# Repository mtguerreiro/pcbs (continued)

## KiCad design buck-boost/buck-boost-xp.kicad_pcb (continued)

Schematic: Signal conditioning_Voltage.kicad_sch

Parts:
C55, C73, C82: tbd; C_0805_2012Metric_Pad1.18x1.45mm_HandSolder
C72: dnp; C_0805_2012Metric_Pad1.18x1.45mm_HandSolder
C76: 1uF; C_0805_2012Metric_Pad1.18x1.45mm_HandSolder
C84: 10nF; C_0805_2012Metric_Pad1.18x1.45mm_HandSolder
R41, R63, R65, R66, R67, R68, R69, R70: tbd; R_0805_2012Metric_Pad1.20x1.40mm_HandSolder
U11: Opamp_Dual; SOIC-8_3.9x4.9mm_P1.27mm

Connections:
/I_out_+: R41.2; also elsewhere on the board
/Measurements/Voltage measurement/Sig_cond_volt_sens2/in_filt: R67.1, R68.1, U11.1, U11.2 (-)
/Measurements/Voltage measurement/Sig_cond_volt_sens2/out_: C72.1, R65.2, R67.2
/Measurements/Voltage measurement/Sig_cond_volt_sens2/out_filt: R66.2, R70.1
/V_dc_out_sens: R65.1, R66.1; also elsewhere on the board
GND: C55.1, C72.2, C76.2, C82.1, C84.2, R63.1, U11.4 (V-); also elsewhere on the board
unnamed: C73.1, R68.2, R69.1
unnamed: C55.2, R41.1, R63.2, U11.3 (+)
unnamed: C82.2, R69.2, U11.5 (+)
unnamed: C73.2, R70.2, U11.6 (-), U11.7
VDD: C76.1, C84.1, U11.8 (V+); also elsewhere on the board

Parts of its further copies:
C54, C56, C69, C78, C81, C83: tbd; C_0805_2012Metric_Pad1.18x1.45mm_HandSolder
C61, C88: 1uF; C_0805_2012Metric_Pad1.18x1.45mm_HandSolder
C62, C89: 10nF; C_0805_2012Metric_Pad1.18x1.45mm_HandSolder
C68, C77: dnp; C_0805_2012Metric_Pad1.18x1.45mm_HandSolder
R40, R42, R55, R56, R57, R58, R59, R60, R64, R72, R73, R74, R75, R76, R77, R78: tbd; R_0805_2012Metric_Pad1.20x1.40mm_HandSolder
U10, U12: Opamp_Dual; SOIC-8_3.9x4.9mm_P1.27mm

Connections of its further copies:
/I_in_-: R40.2; also elsewhere on the board
/Measurements/Voltage measurement/Sig_cond_volt_sens1/in_filt: R56.1, R57.1, U10.1, U10.2 (-)
/Measurements/Voltage measurement/Sig_cond_volt_sens1/out_: C68.1, R56.2, R60.2
/Measurements/Voltage measurement/Sig_cond_volt_sens1/out_filt: R59.1, R64.2
/Measurements/Voltage measurement/Sig_cond_volt_sens3/in_filt: R75.1, R76.1, U12.1, U12.2 (-)
/Measurements/Voltage measurement/Sig_cond_volt_sens3/out_: C77.1, R73.2, R75.2
/Measurements/Voltage measurement/Sig_cond_volt_sens3/out_filt: R74.2, R78.1
/V_dc_in_sens: R60.1, R64.1; also elsewhere on the board
/V_out: R42.2; also elsewhere on the board
/V_out_sens: R73.1, R74.1; also elsewhere on the board
GND: C54.1, C56.1, C61.2, C62.2, C68.2, C77.2, C81.1, C83.1, C88.2, C89.2, R55.1, R72.1, U10.4 (V-), U12.4 (V-); also elsewhere on the board
unnamed: C69.1, R57.2, R58.1
unnamed: C78.1, R76.2, R77.1
unnamed: C54.2, R40.1, R55.2, U10.3 (+)
unnamed: C81.2, R58.2, U10.5 (+)
unnamed: C69.2, R59.2, U10.6 (-), U10.7
unnamed: C56.2, R42.1, R72.2, U12.3 (+)
unnamed: C83.2, R77.2, U12.5 (+)
unnamed: C78.2, R78.2, U12.6 (-), U12.7
VDD: C61.1, C62.1, C88.1, C89.1, U10.8 (V+), U12.8 (V+); also elsewhere on the board

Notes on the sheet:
[3]
[5]
[1] This capacitor is for testing purposes. Ideally we would not need it, and we filter the signal afterwards anyways. [2] This RC network can be used to give some kind of low pass filter at the amplifier's output. Just remember that if you use this, the output is not buffered anymore. If the RC ne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
[1]
[2]
[4]

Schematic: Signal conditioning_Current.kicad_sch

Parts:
C85: dnp; C_0805_2012Metric_Pad1.18x1.45mm_HandSolder
C86, C87: tbd; C_0805_2012Metric_Pad1.18x1.45mm_HandSolder
C105: 1uF; C_0805_2012Metric_Pad1.18x1.45mm_HandSolder
C106: 10nF; C_0805_2012Metric_Pad1.18x1.45mm_HandSolder
R80, R81, R82, R83, R84, R85, R86: tbd; R_0805_2012Metric_Pad1.20x1.40mm_HandSolder
U15: Opamp_Dual; SOIC-8_3.9x4.9mm_P1.27mm

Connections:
/I_in_sens: R81.1, R82.1; also elsewhere on the board
/Measurements/Current measurement/I_in: R80.2, U15.3 (+); also elsewhere on the board
/Measurements/Current measurement/sig_cond_curr_sens1/in_filt: R83.1, R84.1, U15.1, U15.2 (-)
/Measurements/Current measurement/sig_cond_curr_sens1/out_: C85.1, R81.2, R83.2
/Measurements/Current measurement/sig_cond_curr_sens1/out_filt: R82.2, R86.1
GND: C85.2, C86.1, C105.2, C106.2, R80.1, U15.4 (V-); also elsewhere on the board
unnamed: C87.1, R84.2, R85.1
unnamed: C86.2, R85.2, U15.5 (+)
unnamed: C87.2, R86.2, U15.6 (-), U15.7
VDD: C105.1, C106.1, U15.8 (V+); also elsewhere on the board

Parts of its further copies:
C57, C58: dnp; C_0805_2012Metric_Pad1.18x1.45mm_HandSolder
C59, C60, C70, C71: tbd; C_0805_2012Metric_Pad1.18x1.45mm_HandSolder
C98, C100: 1uF; C_0805_2012Metric_Pad1.18x1.45mm_HandSolder
C99, C104: 10nF; C_0805_2012Metric_Pad1.18x1.45mm_HandSolder
R43, R44, R45, R46, R47, R48, R49, R50, R51, R61, R62, R71, R79, R87: tbd; R_0805_2012Metric_Pad1.20x1.40mm_HandSolder
U13, U14: Opamp_Dual; SOIC-8_3.9x4.9mm_P1.27mm

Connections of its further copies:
/IL_sens: R44.1, R61.1; also elsewhere on the board
/I_out_sens: R46.1, R47.1; also elsewhere on the board
/Measurements/Current measurement/I_L: R43.2, U13.3 (+); also elsewhere on the board
/Measurements/Current measurement/I_out: R45.2, U14.3 (+); also elsewhere on the board
/Measurements/Current measurement/sig_cond_curr_sens2/in_filt: R62.1, R71.1, U13.1, U13.2 (-)
/Measurements/Current measurement/sig_cond_curr_sens2/out_: C57.1, R44.2, R62.2
/Measurements/Current measurement/sig_cond_curr_sens2/out_filt: R61.2, R87.1
/Measurements/Current measurement/sig_cond_curr_sens3/in_filt: R48.1, R49.1, U14.1, U14.2 (-)
/Measurements/Current measurement/sig_cond_curr_sens3/out_: C58.1, R46.2, R48.2
/Measurements/Current measurement/sig_cond_curr_sens3/out_filt: R47.2, R51.1
GND: C57.2, C58.2, C59.1, C70.1, C98.2, C99.2, C100.2, C104.2, R43.1, R45.1, U13.4 (V-), U14.4 (V-); also elsewhere on the board
unnamed: C60.1, R49.2, R50.1
unnamed: C71.1, R71.2, R79.1
unnamed: C70.2, R79.2, U13.5 (+)
unnamed: C71.2, R87.2, U13.6 (-), U13.7
unnamed: C59.2, R50.2, U14.5 (+)
unnamed: C60.2, R51.2, U14.6 (-), U14.7
VDD: C98.1, C99.1, C100.1, C104.1, U13.8 (V+), U14.8 (V+); also elsewhere on the board

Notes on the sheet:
[5]
[1] This pull-down resistor was placed here just to present some kind of small load to the sensor's output. Also, this prevents the amplifier's input to ever float. I'm not really sure whether this makes a difference or not. [Future notes: maybe it is better to move this resistor to the output of t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
[3]
[1]
[2]
[4]

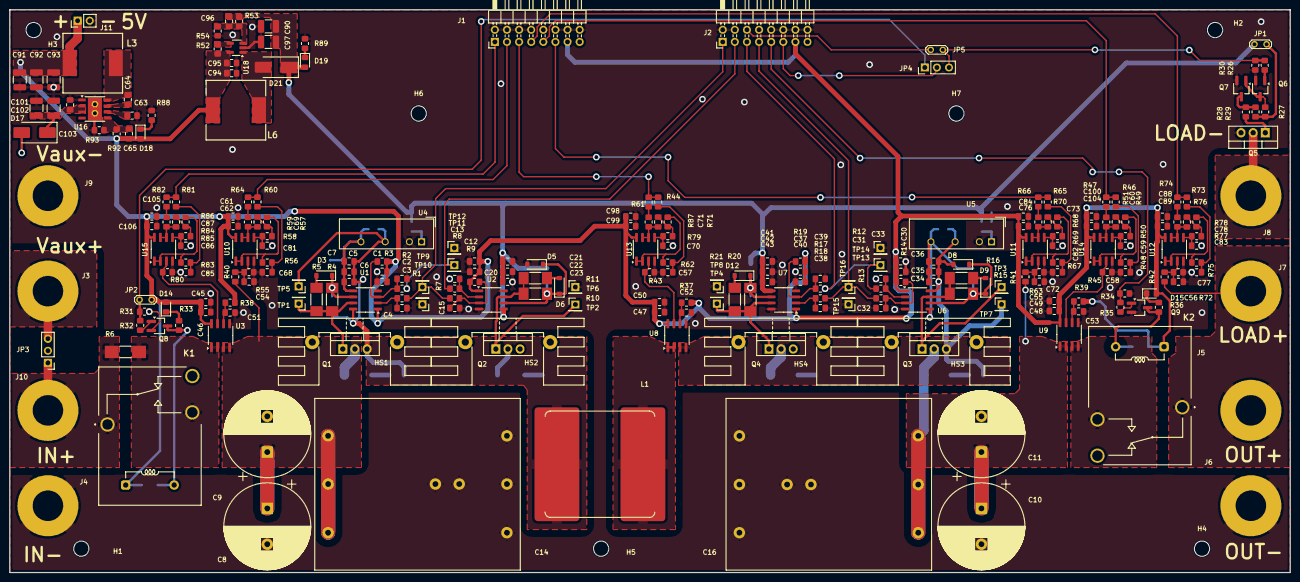
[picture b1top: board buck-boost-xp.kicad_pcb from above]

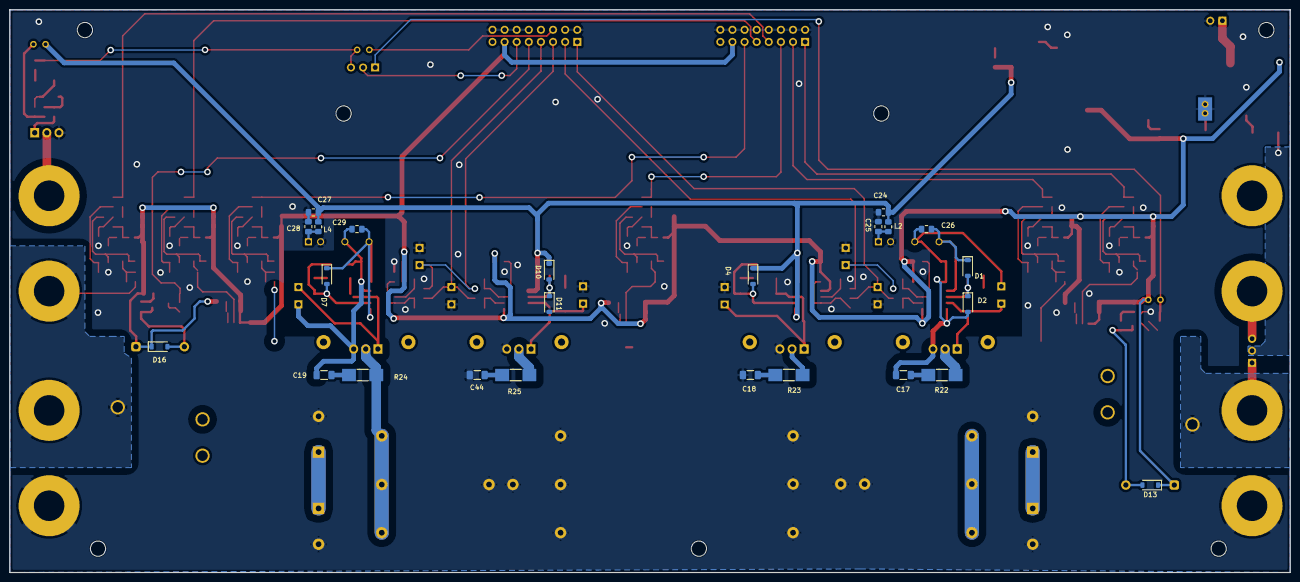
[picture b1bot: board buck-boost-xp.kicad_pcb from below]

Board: 2 copper layers, 268.5 x 118.0 mm, 287 parts (24 on the bottom side), 124 nets.

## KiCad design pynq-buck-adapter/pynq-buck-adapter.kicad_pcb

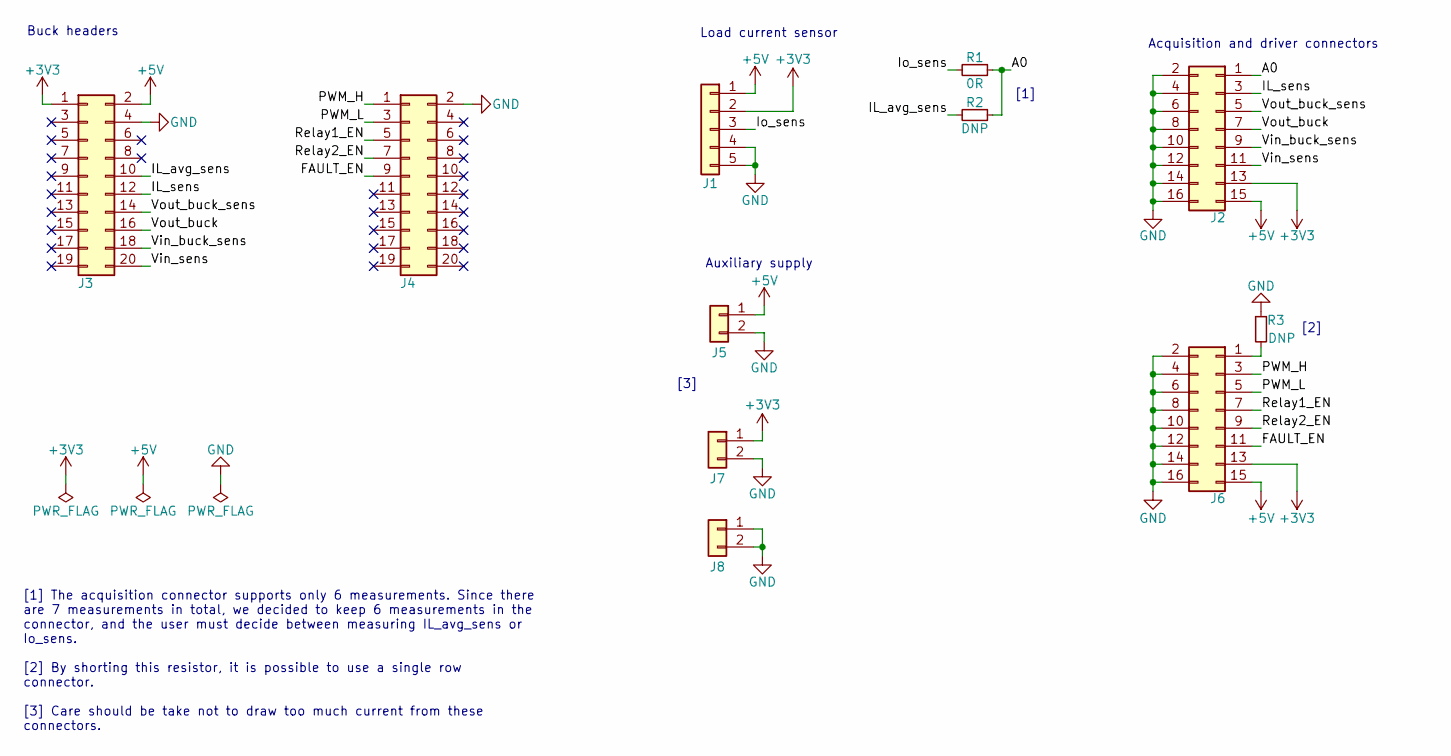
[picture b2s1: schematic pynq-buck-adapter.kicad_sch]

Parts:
J1: Conn_01x05; PinHeader_1x05_P2.54mm_Vertical
J2, J6: Conn_02x08_Odd_Even; PinHeader_2x08_P2.54mm_Horizontal
J3, J4: Conn_02x10_Odd_Even; PinHeader_2x10_P2.54mm_Vertical
J5, J7, J8: Conn_01x02; PinHeader_1x02_P2.54mm_Vertical
R1: 0R; R_0805_2012Metric_Pad1.20x1.40mm_HandSolder
R2, R3: DNP; R_0805_2012Metric_Pad1.20x1.40mm_HandSolder

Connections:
+3V3: J1.2, J2.13, J3.1, J6.13, J7.1
+5V: J1.1, J2.15, J3.2, J5.1, J6.15
/A0: J2.1, R1.1, R2.1
/FAULT_EN: J4.9, J6.11
/IL_avg_sens: J3.10, R2.2
/IL_sens: J2.3, J3.12
/Io_sens: J1.3, R1.2
/PWM_H: J4.1, J6.3
/PWM_L: J4.3, J6.5
/Relay1_EN: J4.5, J6.7
/Relay2_EN: J4.7, J6.9
/Vin_buck_sens: J2.9, J3.18
/Vin_sens: J2.11, J3.20
/Vout_buck: J2.7, J3.16
/Vout_buck_sens: J2.5, J3.14
GND: J1.4, J1.5, J2.2, J2.4, J2.6, J2.8, J2.10, J2.12, J2.14, J2.16, J3.4, J4.2, J5.2, J6.2, J6.4, J6.6, J6.8, J6.10, J6.12, J6.14, J6.16, J7.2, J8.1, J8.2, R3.1
unnamed: J6.1, R3.2

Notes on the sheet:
[1] The acquisition connector supports only 6 measurements. Since there are 7 measurements in total, we decided to keep 6 measurements in the connector, and the user must decide between measuring IL_avg_sens or Io_sens. [2] By shorting this resistor, it is possible to use a single row connector. [3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
[2]
[1]
Load current sensor
[3]
Buck headers
Acquisition and driver connectors
Auxiliary supply

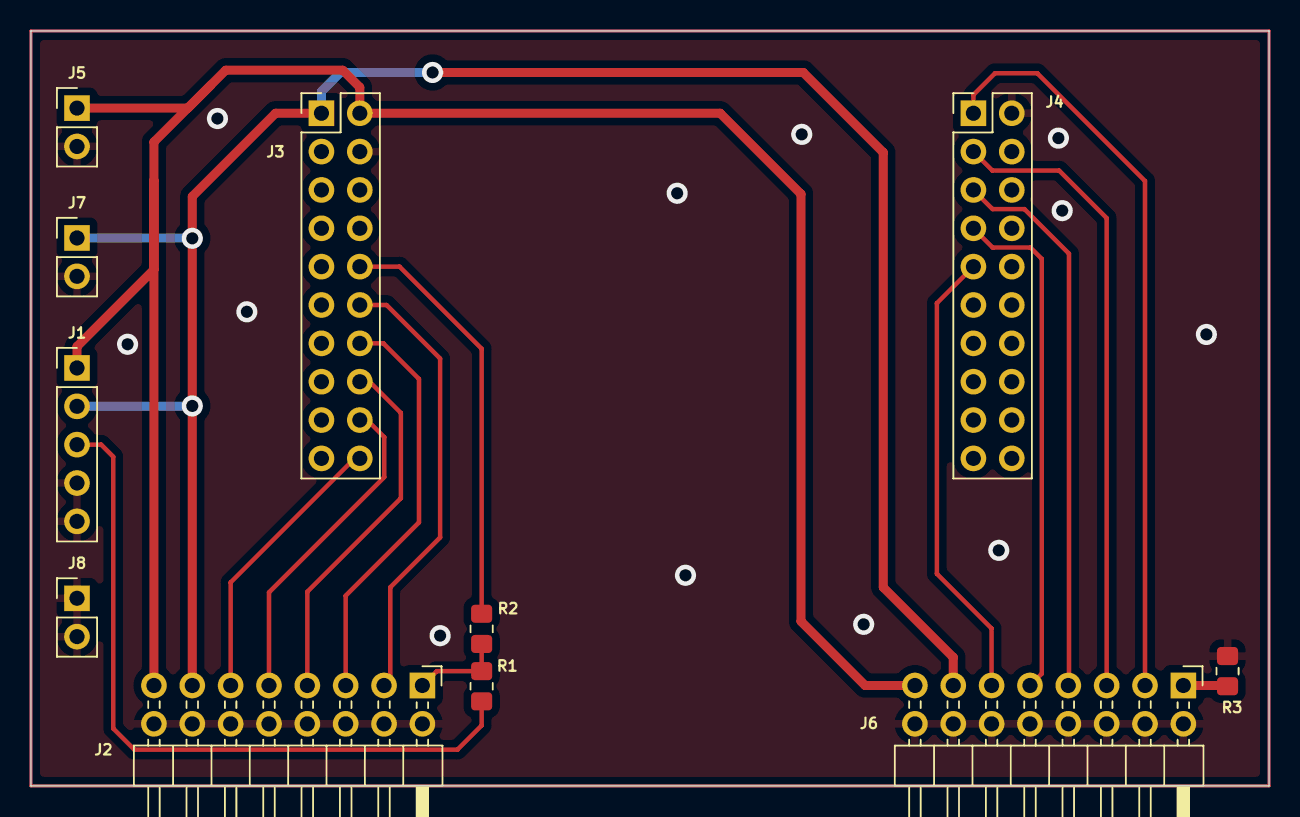
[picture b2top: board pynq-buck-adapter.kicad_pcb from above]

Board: 2 copper layers, 82.0 x 50.0 mm, 11 parts (0 on the bottom side), 17 nets.

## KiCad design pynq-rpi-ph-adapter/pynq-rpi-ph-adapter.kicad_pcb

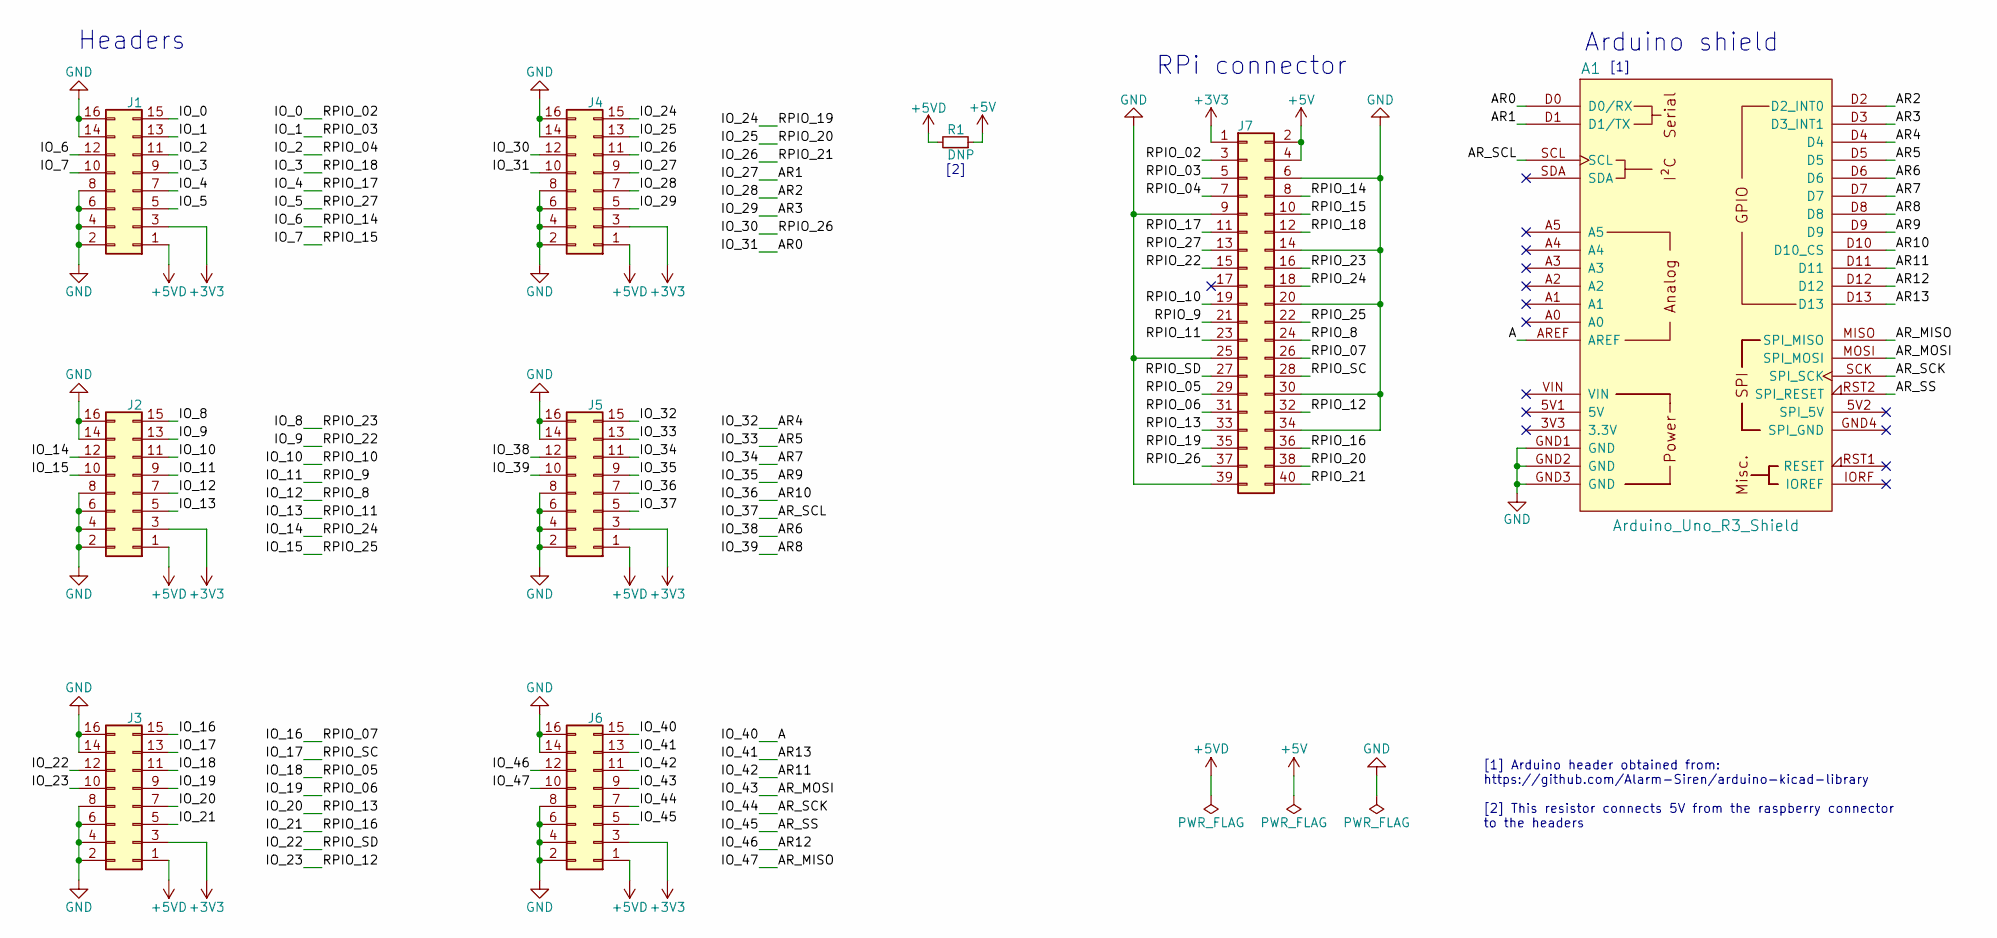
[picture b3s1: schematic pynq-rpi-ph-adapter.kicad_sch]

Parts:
A1: Arduino_Uno_R3_Shield; Arduino_Uno_R3_Shield_No_MH
J1, J2, J3, J4, J5, J6: Conn_02x08_Odd_Even; PinHeader_2x08_P2.54mm_Horizontal
J7: Conn_02x20_Odd_Even; PinHeader_2x20_P2.54mm_Vertical
R1: DNP; R_0805_2012Metric

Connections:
+3V3: J1.3, J2.3, J3.3, J4.3, J5.3, J6.3, J7.1
+5V: J7.2, J7.4, R1.1
+5VD: J1.1, J2.1, J3.1, J4.1, J5.1, J6.1, R1.2
/A: A1.AREF, J6.15
/AR0: A1.D0 (D0/RX), J4.10
/AR1: A1.D1 (D1/TX), J4.9
/AR2: A1.D2 (D2_INT0), J4.7
/AR3: A1.D3 (D3_INT1), J4.5
/AR4: A1.D4, J5.15
/AR5: A1.D5, J5.13
/AR6: A1.D6, J5.12
/AR7: A1.D7, J5.11
/AR8: A1.D8, J5.10
/AR9: A1.D9, J5.9
/AR10: A1.D10 (D10_CS), J5.7
/AR11: A1.D11, J6.11
/AR12: A1.D12, J6.12
/AR13: A1.D13, J6.13
/AR_MISO: A1.MISO (SPI_MISO), J6.10
/AR_MOSI: A1.MOSI (SPI_MOSI), J6.9
/AR_SCK: A1.SCK (SPI_SCK), J6.7
/AR_SCL: A1.SCL, J5.5
/AR_SS: A1.RST2 (SPI_RESET), J6.5
/IO_0: J1.15, J7.3
/IO_1: J1.13, J7.5
/IO_2: J1.11, J7.7
/IO_3: J1.9, J7.12
/IO_4: J1.7, J7.11
/IO_5: J1.5, J7.13
/IO_6: J1.12, J7.8
/IO_7: J1.10, J7.10
/IO_8: J2.15, J7.16
/IO_9: J2.13, J7.15
/IO_10: J2.11, J7.19
/IO_11: J2.9, J7.21
/IO_12: J2.7, J7.24
/IO_13: J2.5, J7.23
/IO_14: J2.12, J7.18
/IO_15: J2.10, J7.22
/IO_16: J3.15, J7.26
/IO_17: J3.13, J7.28
/IO_18: J3.11, J7.29
/IO_19: J3.9, J7.31
/IO_20: J3.7, J7.33
/IO_21: J3.5, J7.36
/IO_22: J3.12, J7.27
/IO_23: J3.10, J7.32
/IO_24: J4.15, J7.35
/IO_25: J4.13, J7.38
/IO_26: J4.11, J7.40
/IO_30: J4.12, J7.37
GND: A1.GND1 (GND), A1.GND2 (GND), A1.GND3 (GND), J1.2, J1.4, J1.6, J1.8, J1.14, J1.16, J2.2, J2.4, J2.6, J2.8, J2.14, J2.16, J3.2, J3.4, J3.6, J3.8, J3.14, J3.16, J4.2, J4.4, J4.6, J4.8, J4.14, J4.16, J5.2, J5.4, J5.6, J5.8, J5.14, J5.16, J6.2, J6.4, J6.6, J6.8, J6.14, J6.16, J7.6, J7.9, J7.14, J7.20, J7.25, J7.30, J7.34, J7.39

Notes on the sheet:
Headers
[2]
RPi connector
[1]
[1] Arduino header obtained from: https://github.com/Alarm-Siren/arduino-kicad-library [2] This resistor connects 5V from the raspberry connector to the headers
Arduino shield

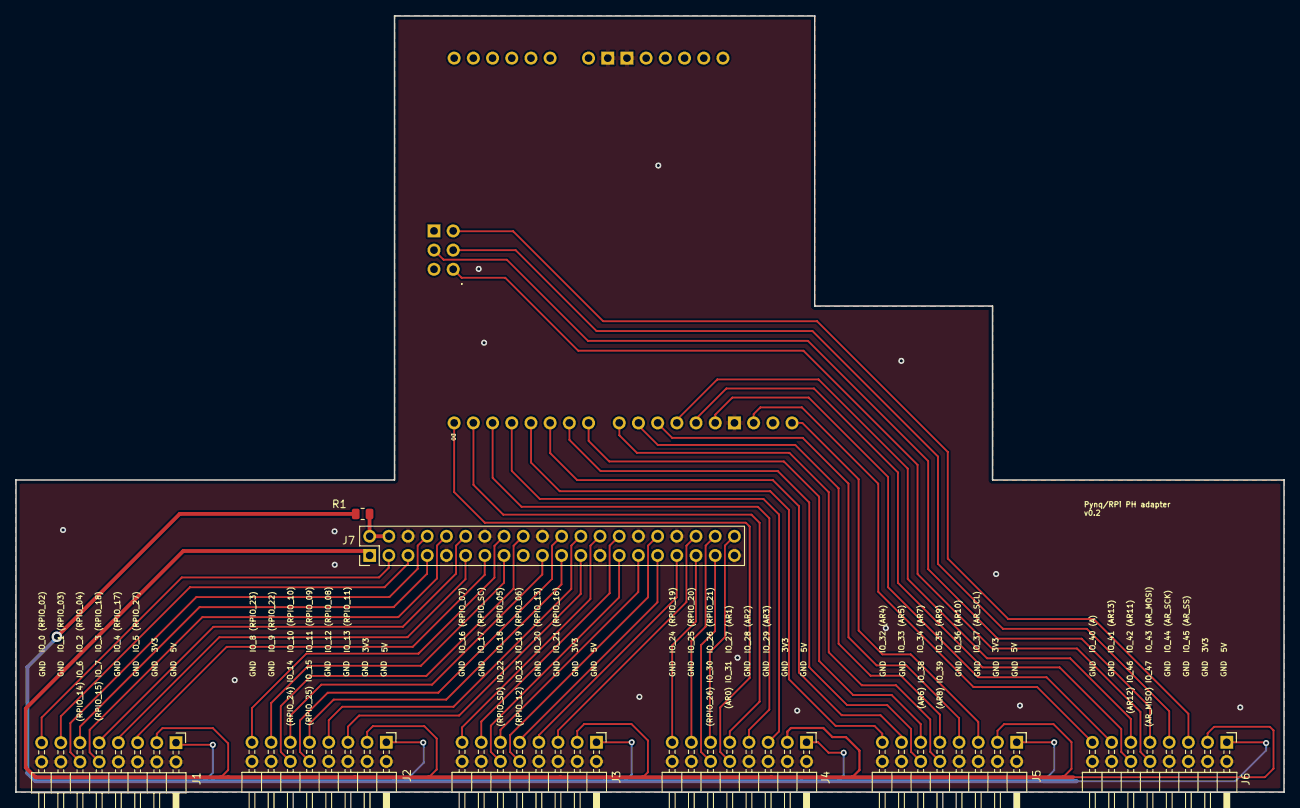
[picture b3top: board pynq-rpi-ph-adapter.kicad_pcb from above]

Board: 2 copper layers, 167.8 x 102.7 mm, 9 parts (0 on the bottom side), 52 nets.

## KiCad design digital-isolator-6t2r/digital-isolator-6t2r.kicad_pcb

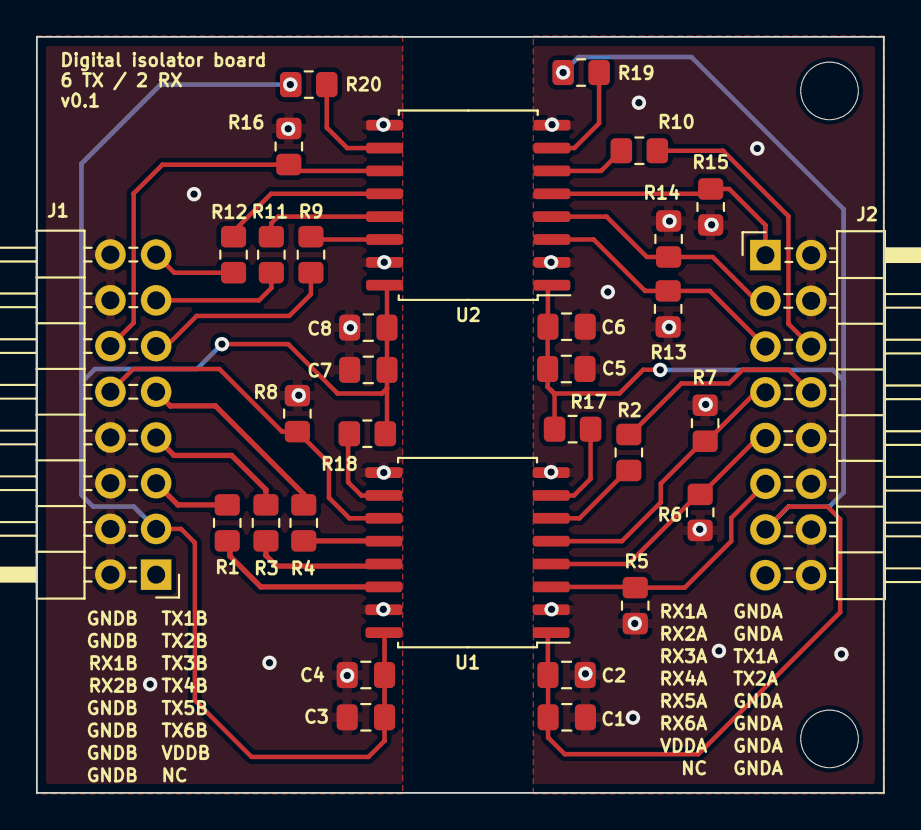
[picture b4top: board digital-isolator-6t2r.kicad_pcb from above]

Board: 2 copper layers, 47.1 x 42.0 mm, 34 parts (0 on the bottom side), 32 nets.

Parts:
C1, C3, C5, C7: 1uF; C_0805_2012Metric_Pad1.18x1.45mm_HandSolder
C2, C4, C6, C8: 100nF; C_0805_2012Metric_Pad1.18x1.45mm_HandSolder
H1, H2: MountingHole; MountingHole_3.2mm_M3
J1, J2: Conn_02x08_Odd_Even; PinHeader_2x08_P2.54mm_Horizontal
R1, R2, R3, R4, R9, R10, R11, R12: 47R; R_0805_2012Metric_Pad1.20x1.40mm_HandSolder
R5, R6, R7, R8, R13, R14, R15, R16, R17, R18, R19, R20: 100k; R_0805_2012Metric_Pad1.20x1.40mm_HandSolder
U1, U2: ADuM1401xRW; SOIC-16W_7.5x10.3mm_P1.27mm

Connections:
/RX1_A: J2.1, R15.1, U2.5 (VIC)
/RX1_B: J1.12, R16.1, U2.11 (VID)
/RX2_A: J2.3, R14.1, U2.4 (VIB)
/RX2_B: J1.10, R8.1, U1.11 (VID)
/RX3_A: J2.5, R13.1, U2.3 (VIA)
/RX4_A: J2.7, R7.1, U1.5 (VIC)
/RX5_A: J2.9, R6.1, U1.4 (VIB)
/RX6_A: J2.11, R5.1, U1.3 (VIA)
/TX1_A: J2.6, R10.2
/TX1_B: J1.15, R12.2
/TX2_A: J2.8, R2.2
/TX2_B: J1.13, R11.2
/TX3_B: J1.11, R9.2
/TX4_B: J1.9, R4.2
/TX5_B: J1.7, R3.2
/TX6_B: J1.5, R1.2
/adum241x1/TX1_A': R2.1, U1.6 (VOD)
/adum241x1/TX1_B': R1.1, U1.14 (VOA)
/adum241x1/TX2_B': R3.1, U1.13 (VOB)
/adum241x1/TX3_B': R4.1, U1.12 (VOC)
/adum241x/TX1_A': R10.1, U2.6 (VOD)
/adum241x/TX1_B': R9.1, U2.14 (VOA)
/adum241x/TX2_B': R11.1, U2.13 (VOB)
/adum241x/TX3_B': R12.1, U2.12 (VOC)
GNDA: C1.2, C2.2, C5.2, C6.2, J2.2, J2.4, J2.10, J2.12, J2.14, J2.16, R5.2, R6.2, R7.2, R13.2, R14.2, R15.2, U1.2 (GND1), U1.8 (GND1), U2.2 (GND1), U2.8 (GND1)
GNDB: C3.2, C4.2, C7.2, C8.2, J1.2, J1.4, J1.6, J1.8, J1.14, J1.16, R8.2, R16.2, U1.9 (GND2), U1.15 (GND2), U2.9 (GND2), U2.15 (GND2)
unnamed: R17.1, U1.7 (VE1)
unnamed: R18.2, U1.10 (VE2)
unnamed: R19.1, U2.7 (VE1)
unnamed: R20.2, U2.10 (VE2)
VDDA: C1.1, C2.1, C5.1, C6.1, J2.13, R17.2, R19.2, U1.1 (VDD1), U2.1 (VDD1)
VDDB: C3.1, C4.1, C7.1, C8.1, J1.3, R18.1, R20.1, U1.16 (VDD2), U2.16 (VDD2)

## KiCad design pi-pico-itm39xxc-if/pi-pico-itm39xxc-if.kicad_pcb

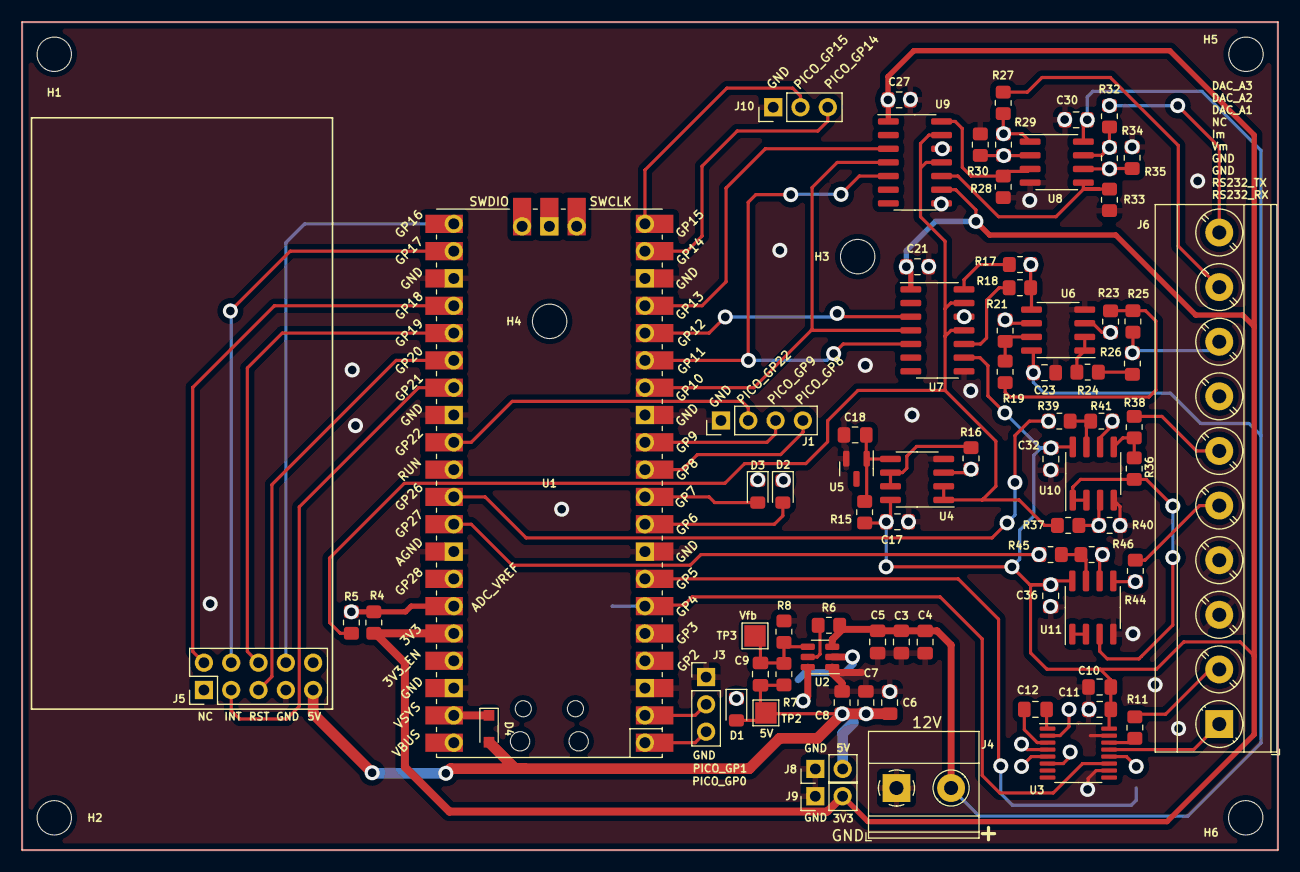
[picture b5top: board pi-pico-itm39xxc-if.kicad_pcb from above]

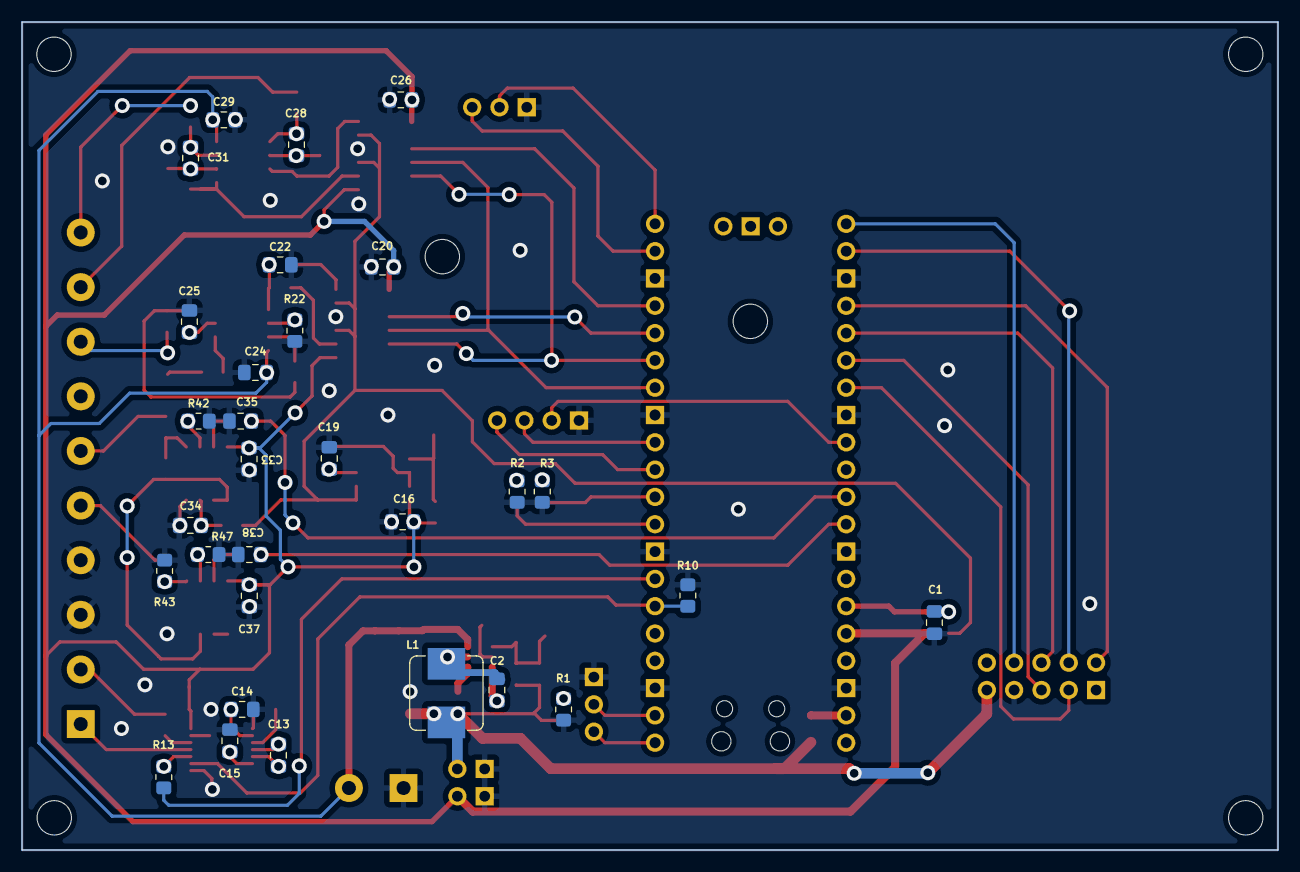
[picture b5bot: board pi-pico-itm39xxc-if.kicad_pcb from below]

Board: 2 copper layers, 116.8 x 77.0 mm, 112 parts (30 on the bottom side), 79 nets.

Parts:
C1, C9, C28, C31, C35, C38: DNP; C_0805_2012Metric_Pad1.18x1.45mm_HandSolder
C2, C5, C11, C12, C17, C18, C21, C23, C27, C30, C32, C34, C36: 100nF; C_0805_2012Metric_Pad1.18x1.45mm_HandSolder
C3, C4, C6, C7, C8: 22uF; C_0805_2012Metric_Pad1.18x1.45mm_HandSolder
C10, C20, C26: 10uF; C_0805_2012Metric_Pad1.18x1.45mm_HandSolder
C13, C14, C15: 470nF; C_0805_2012Metric_Pad1.18x1.45mm_HandSolder
C16, C19, C24, C29, C33, C37: 1uF; C_0805_2012Metric_Pad1.18x1.45mm_HandSolder
C22: 1nF; C_0805_2012Metric_Pad1.18x1.45mm_HandSolder
C25: 0R; C_0805_2012Metric_Pad1.18x1.45mm_HandSolder
D1, D2, D3: LED_Small_Filled; LED_0805_2012Metric_Pad1.15x1.40mm_HandSolder
D4: BAT60; D_SOD-323_HandSoldering
H1, H2, H3, H4, H5, H6: MountingHole; MountingHole_3.2mm_M3
J1: Conn_01x04; PinHeader_1x04_P2.54mm_Vertical
J3, J10: Conn_01x03; PinHeader_1x03_P2.54mm_Vertical
J4: Conn_01x02; TerminalBlock_Phoenix_MKDS-1,5-2-5.08_1x02_P5.08mm_Horizont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
J5: Conn_02x05_Odd_Even; PinHeader_2x05_P2.54mm_Vertical
J6: Conn_01x10; TerminalBlock_Phoenix_MKDS-3-10-5.08_1x10_P5.08mm_Horizontal
J8, J9: Conn_01x02; PinHeader_1x02_P2.54mm_Vertical
L1: 4.7uH; L_Bourns_SRP7028A_7.3x6.6mm
R1, R8, R15: 2k; R_0805_2012Metric_Pad1.20x1.40mm_HandSolder
R2, R3: 1k; R_0805_2012Metric_Pad1.20x1.40mm_HandSolder
R4, R23, R24, R25, R28, R33: DNP; R_0805_2012Metric_Pad1.20x1.40mm_HandSolder
R5, R11, R13: 47R; R_0805_2012Metric_Pad1.20x1.40mm_HandSolder
R6, R10, R16, R37, R40, R44, R47: 10k; R_0805_2012Metric_Pad1.20x1.40mm_HandSolder
R7: 11k; R_0805_2012Metric_Pad1.20x1.40mm_HandSolder
R17, R21, R29, R34: 56k; R_0805_2012Metric_Pad1.20x1.40mm_HandSolder
R18, R22, R30, R35: 24k; R_0805_2012Metric_Pad1.20x1.40mm_HandSolder
R19, R27, R32: 22R; R_0805_2012Metric_Pad1.20x1.40mm_HandSolder
R26, R39, R45: 0R; R_0805_2012Metric_Pad1.20x1.40mm_HandSolder
R36, R41, R43, R46: 3k; R_0805_2012Metric_Pad1.20x1.40mm_HandSolder
R38, R42: 20k; R_0805_2012Metric_Pad1.20x1.40mm_HandSolder
TP2, TP3: TestPoint_Small; TestPoint_Pad_2.0x2.0mm
U1: Pico; RPi_Pico_SMD_TH
U2: TPS56320x; SOT-23-6
U3: MAX3232; TSSOP-16_4.4x5mm_P0.65mm
U4, U6, U8, U10, U11: Opamp_Dual; SOIC-8_3.9x4.9mm_P1.27mm
U5: LM4040DBZ-3; SOT-23
U7, U9: MCP4922; SOIC-14_3.9x8.7mm_P1.27mm

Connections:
+3V3: C10.1, C11.1, C16.1, C17.1, C20.1, C21.1, C26.1, C27.1, C32.1, C33.1, C36.1, C37.1, J9.2, R4.1, R15.1, U1.36 (3V3), U3.16 (VCC), U4.8 (V+), U7.1 (Vdd), U7.9 (~SHDN), U9.1 (Vdd), U9.9 (~SHDN), U10.8 (V+), U11.8 (V+)
+5V: C6.1, C7.1, C8.1, C9.1, D1.2 (A), D4.2 (A), J5.9, J8.2, L1.2, R7.1, TP2.1
+12V: C3.1, C4.1, C5.1, C23.1, C24.1, C29.1, C30.1, J4.2, R6.2, U2.3 (VIN), U6.8 (V+), U8.8 (V+)
/ADC_VREF: C1.1, R4.2, R5.2, U1.35 (ADC_VREF)
/DAC_A1: J6.8, R25.2, R26.2
/DAC_A1_~CS: U1.16 (GPIO12), U7.3 (~CS)
/DAC_A2: J6.9, R27.1
/DAC_A2_A3_~CS: U1.17 (GPIO13), U9.3 (~CS)
/DAC_A3: J6.10, R32.1
/DAC_REF: R5.1, R37.1, U4.1, U4.2 (-), U7.11 (VrefB), U7.13 (VrefA), U9.11 (VrefB), U9.13 (VrefA)
/DAC_SCLK: U1.14 (GPIO10), U7.4 (SCK), U9.4 (SCK)
/DAC_SD: U1.15 (GPIO11), U7.5 (SDI), U9.5 (SDI)
/Im: J6.6, R38.1
/Im_ADC: C35.1, R39.2, U1.31 (GPIO26_ADC0)
/LED_1: D2.2 (A), U1.9 (GPIO6)
/LED_2: D3.2 (A), U1.10 (GPIO7)
/PICO_GPIO0: J3.3, U1.1 (GPIO0)
/PICO_GPIO1: J3.2, U1.2 (GPIO1)
/PICO_GPIO4: R10.2, U1.6 (GPIO4), U3.11 (T1IN)
/PICO_GPIO5: R13.2, U1.7 (GPIO5)
/PICO_GPIO8: J1.4, U1.11 (GPIO8)
/PICO_GPIO9: J1.3, U1.12 (GPIO9)
/PICO_GPIO14: J10.3, U1.19 (GPIO14)
/PICO_GPIO15: J10.2, U1.20 (GPIO15)
/PICO_GPIO16: J5.8, U1.21 (GPIO16)
/PICO_GPIO17: J5.4, U1.22 (GPIO17)
/PICO_GPIO18: J5.2, U1.24 (GPIO18)
/PICO_GPIO19: J5.6, U1.25 (GPIO19)
/PICO_GPIO20: J5.5, U1.26 (GPIO20)
/PICO_GPIO21: J5.3, U1.27 (GPIO21)
/PICO_GPIO22: J1.2, U1.29 (GPIO22)
/PICO_GPIO27: C38.1, R45.2, U1.32 (GPIO27_ADC1)
/RS232_RX1: J6.1, U3.13 (R1IN)
/RS232_TX1: J6.2, R11.1
/Vm: J6.5, R44.1
/dac_module/DAC_2_OUT: R28.1, U8.3 (+), U9.14 (VA)
/dac_module/DAC_3_OUT: R33.1, U8.5 (+), U9.10 (VB)
/dac_module/V_coarse: R18.1, U7.10 (VB)
/dac_module/V_dac_1: R19.2, R23.1, R25.1
/dac_module/V_dac_1_buf: R24.2, R26.1
/dac_module/V_fine: R17.1, U7.14 (VA)
/itm39xxc_meas_cond/V_ref': R36.1, U10.1, U10.2 (-), U11.3 (+)
/tps56320x_5v/VFB: C9.2, R7.2, R8.1, TP3.1, U2.4 (VFB)
GND: C1.2, C3.2, C4.2, C5.2, C6.2, C7.2, C8.2, C10.2, C11.2, C14.2, C15.2, C16.2, C17.2, C18.2, C19.2, C20.2, C21.2, C22.2, C23.2, C24.2, C25.2, C26.2, C27.2, C29.2, C30.2, C32.2, C33.2, C34.2, C35.2, C36.2, C37.2, C38.2, J1.1, J3.1, J4.1, J5.7, J6.3, J6.4, J8.1, J9.1, J10.1, R1.2, R2.2, R3.2, R8.2, R10.1, R22.2, R28.2, R30.1, R33.2, R35.1, R40.2, R42.2, R43.1, R47.2, U1.3 (GND), U1.8 (GND), U1.13 (GND), U1.18 (GND), U1.23 (GND), U1.28 (GND), U1.33 (AGND), U1.38 (GND), U2.1 (GND), U3.10 (T2IN), U3.15 (GND), U4.4 (V-), U5.2 (A), U6.4 (V-), U7.8 (~LDAC), U7.12 (Vss), U8.4 (V-), U9.8 (~LDAC), U9.12 (Vss), U10.4 (V-), U11.4 (V-)
unnamed: C2.1, L1.1, U2.2 (SW)
unnamed: C2.2, U2.6 (VBST)
unnamed: C12.1, U3.1 (C1+)
unnamed: C12.2, U3.3 (C1-)
unnamed: C13.1, U3.4 (C2+)
unnamed: C13.2, U3.5 (C2-)
unnamed: C14.1, U3.2 (VS+)
unnamed: C15.1, U3.6 (VS-)
unnamed: C18.1, R15.2, U4.5 (+), U5.1 (K)
unnamed: C19.1, R16.2, U4.3 (+)
unnamed: C22.1, R17.2, R18.2, U6.5 (+)
unnamed: C25.1, R23.2, U6.3 (+)
unnamed: C28.1, R29.1, R30.2, U8.2 (-)
unnamed: C28.2, R27.2, R29.2, U8.1
unnamed: C31.1, R34.1, R35.2, U8.6 (-)
unnamed: C31.2, R32.2, R34.2, U8.7
unnamed: C34.1, R37.2, R40.1, U10.3 (+)
unnamed: D1.1 (K), R1.1
unnamed: D2.1 (K), R2.1
unnamed: D3.1 (K), R3.1
unnamed: D4.1 (K), U1.39 (VSYS)
unnamed: R6.1, U2.5 (EN)
unnamed: R11.2, U3.14 (T1OUT)
unnamed: R13.1, U3.12 (R1OUT)
unnamed: R16.1, U4.6 (-), U4.7
unnamed: R19.1, R21.2, U6.7
unnamed: R21.1, R22.1, U6.6 (-)
unnamed: R24.1, U6.1, U6.2 (-)
unnamed: R36.2, R38.2, U10.5 (+)
unnamed: R39.1, R41.2, U10.7
unnamed: R41.1, R42.1, U10.6 (-)
unnamed: R43.2, R44.2, U11.5 (+)
unnamed: R45.1, R46.2, U11.7
unnamed: R46.1, R47.1, U11.6 (-)
unnamed: U11.1, U11.2 (-)
